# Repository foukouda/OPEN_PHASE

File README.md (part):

<h1 align="center">OPEN_PHASE – PHASETRACKER</h1>

<p align="center">
  3-phase inline current and voltage sensing PCB for BLDC drone motors (INA241A4 + AD7606C-18)
</p>

<p align="center">
  Sub-project of <a href="https://opentruslab.vercel.app/">OPEN THRUST LAB</a>
</p>

<p align="center" width="100%">

</p>

<p align="center">
  
&nbsp; &nbsp; &nbsp; &nbsp;
  
</p>

<p align="center">
  
  <br><sub>Full-resolution video, 60 fps: <a href="Images/OPEN_PHASE.mp4">Images/OPEN_PHASE.mp4</a> (KiCad raytracing, <code>kicad-cli pcb render</code>)</sub>
</p>

***

## OVERVIEW

**OPEN_PHASE** is an open-hardware measurement board developed as part of **OPEN THRUST LAB**, a community-driven project building open-source test benches for drone motor characterization.

The board is inserted between the ESC and a 3-phase BLDC motor (two Amass **MR60PW** connectors) and between the battery and the ESC (two Amass **XT60PW** connectors). On each motor phase (U, V, W) and on the battery line (B) it measures:

- the **current**, with a 1 mΩ four-terminal shunt (Isabellenhütte PBV-R001) and a **TI INA241A4** current-sense amplifier (100 V/V, enhanced PWM rejection, bidirectional around a 2.5 V reference);
- the **voltage**, with a 40.2 kΩ / 10 kΩ divider.

The eight signals are sampled **simultaneously** by an **Analog Devices AD7606C-18** (8 channels, 18 bits, 1 MSPS), so that power, efficiency and ESC behaviour can be computed from time-aligned Vu/Vv/Vw, Iu/Iv/Iw and the battery voltage and current Vb/Ib.

The board only needs **3.3 V**. An LT8362 boost converter (2 MHz) makes 6 V, and two LT3045-1 ultralow-noise LDOs make the analog rails. Each LDO has its SET pin driven by an LTC6655 precision reference, so the LDO works as a low-noise buffer for the reference: **+5VA** (ADC and amplifier supply) and **+2.5VA** (ADC reference and amplifier zero-current level).

> This project was first published as **PhaseSense-8586**, after the first version of the design (INA240 + ADS8586S). The schematic now uses the **INA241A4** and the **AD7606C-18**; everything in this README is taken from the current netlist.

***

## STATUS

This revision has **no ERC / DRC error left**, but it is **not ordered yet**: every fitted part has a manufacturer part number, but there is no firmware. What is in the repository today:

| Area | State |
| --- | --- |
| Analog front-end (shunts, INA241A4, dividers, input filters) | Drawn and routed |
| AD7606C-18 supply, reference and analog inputs | Drawn and routed |
| AD7606C-18 digital interface (CONVST, BUSY, CS, SCLK, SDI, DOUTA–D, RESET, FRSTDATA) | Drawn: software mode (OS0–2 high), serial (PAR/SER SEL high), external reference (REF SELECT low), to the host connector J4. Drawn and routed |
| +3.3V input | J4 pin 1, from the host |
| Power supply (LT8362, LTC6655, LT3045-1) | Drawn and routed. D6 (PMEG2020EH, +3.3V to +5VA) keeps AVCC within 0.3 V of VDRIVE at power-up |
| BOM | Manufacturer and part number on every fitted part (`Manufacturer_Name`, `Manufacturer_Part_Number`). Passives: Murata / Samsung MLCC (C0G for the filters, X7R / X5R rated 16 V or more on the 5–6 V rails), Yageo RC 1 % thick film (the tolerance of simulation 08), Bourns CAT16 arrays. LEDs Würth 150060RS75000, J4 Würth 61301621021 |
| ERC / DRC | ERC 0; DRC 0 errors, 8 warnings (4 copper slivers on In2, 4 footprints edited on the board: IC1, J3, J4, J5); schematic parity 0. CI runs the `PRELIMINARY` variant (no ERC/DRC gate) |

See [DESIGN REVIEW](#design-review) for the points found while documenting and simulating the design.

***

## SPECIFICATIONS

### Electrical specifications

| Parameter | Value |
| --- | --- |
| Input voltage | 3.3 V (LT8362 input range starts at 2.8 V) |
| Boost output — LT8362 | 5.98 V, 2 MHz (RT = 20 kΩ), FBX divider R5/R6 = 1 MΩ / 365 kΩ |
| Analog supply +5VA | 5.000 V — LTC6655-5 (IC7) driving the SET pin of an LT3045-1 (IC8) through R8 = 1 kΩ |
| Reference rail +2.5VA | 2.500 V — LTC6655-2.5 (IC3) driving the SET pin of an LT3045-1 (IC9) through R11 = 1 kΩ |
| Digital supply (AD7606C VDRIVE) | 3.3 V, from the host |
| ADC | AD7606C-18, 8-channel simultaneous sampling, 18 bits, 1 MSPS, external reference on REFIN/REFOUT |
| Current sensing | 4 × PBV-R001 1 mΩ shunt + INA241A4 (100 V/V): **100 mV/A**, zero current = 2.5 V. Version A4 of the silkscreen table, for small motors (1205.5 on 1S); A2 (20 mV/A) for large motors |
| Current range | The amplifier output swing allows about ±23 A (18 A peak in the version table). Connectors: 35 A continuous on the phases (MR60PW), 30 A on the battery line (XT60PW) |
| Voltage sensing | 4 × divider 40.2 kΩ / 10 kΩ: 0.1992 V/V unloaded, **0.1977 V/V** with the AD7606C input impedance |
| Voltage range | 50 V on a ±10 V ADC range (25.2 V for a 6S pack gives 4.98 V) |
| Current channel bandwidth | 17.5 kHz (phase U: R15 = 33 Ω, R16 = 9.1 kΩ, C25 = 1 nF) |
| Voltage channel bandwidth | 48.5 kHz (phase U: divider + Re1 = 1 kΩ, R19 = 9.1 kΩ, C31 = 180 pF) |
| Phase connectors | 2 × Amass MR60PW (J1 = IN-U/V/W from the ESC, J2 = OUT-U/V/W to the motor), 35 A |
| Battery connectors | 2 × Amass XT60PW (J3 = IN-B from the battery, J5 = OUT-B to the ESC), 30 A |

### ADC channel assignment

| AD7606C input | Signal | Source |
| --- | --- | --- |
| V1 | Battery voltage | OUT-B, R32 / R33, Re4, C40, R34 |
| V2 | Battery current | R9 shunt, IC10, R30, C42, R31 |
| V3 | Phase W voltage | OUT-W, R27 / R28, Re3, C34, R29 |
| V4 | Phase W current | R7 shunt, IC6, R25, C33, R26 |
| V5 | Phase V voltage | OUT-V, R22 / R23, Re2, C32, R24 |
| V6 | Phase V current | R4 shunt, IC4, R20, C29, R21 |
| V7 | Phase U voltage | OUT-U, R17 / R18, Re1, C31, R19 |
| V8 | Phase U current | R1 shunt, IC2, R15, C25, R16 |

The four channels are numbered alike: Rn = 33 Ω and Rn+1 = 9.1 kΩ (current filter), Rn+2 / Rn+3 = divider, Rn+4 = 9.1 kΩ (voltage filter), with n = 15 (U), 20 (V), 25 (W), 30 (B). Re1 … Re4 are the 1 kΩ series resistors of the voltage filters.

Current sign: IN+ of each INA241 is on the output side of the shunt (J2 for the phases, J5 for the battery), so a current flowing **from J1 to J2**, or from J3 to J5, **lowers** the output: `V = 2.5 V − 100 mV/A × I(J1→J2)`. The voltage is measured on the same output side of the shunt.

### Power budget

Power chain: **+3.3 V (host) → LT8362 → +6 V → LTC6655 + LT3045-1 → +5VA / +2.5VA**

| Load | Rail | Typical current |
| --- | --- | --- |
| AD7606C-18 AVCC (datasheet: 8.5 mA at 10 kSPS, 45 mA at 1 MSPS) | +5VA | 8.5 – 45 mA |
| 4 × INA241A4 (2.5 mA each) | +5VA | 10 mA |
| 2 × LTC6655 (5 mA each) and 2 × LT3045-1 | +6V | ≈ 13 mA |
| **Total on +6V** (simulated, 1 MSPS) | **+6V** | **68 mA** |
| AD7606C-18 VDRIVE | +3.3V | < 2 mA |
| **Board total** (simulated, 1 MSPS) | **+3.3V** | **≈ 133 mA (0.44 W)** |

### Physical specifications

| Parameter | Value |
| --- | --- |
| Project name | OPEN_PHASE |
| Board name | PHASETRACKER |
| Parent project | OPEN THRUST LAB |
| CAD tool | KiCad 10 |
| Automation tooling | KiBot + GitHub Actions |
| Hardware licence | CERN-OHL-P v2 |
| Dimensions | 65.05 × 77.5 mm |
| Stackup | 4 layers, 1.66 mm, 70 µm outer copper, ENIG |
| Mounting holes | 4 × M3, connected to GND |

***

## SCHEMATIC ARCHITECTURE

Five functional hierarchical sheets (under `Project Architecture`), plus the documentation sheets (Block Diagram, Power - Sequencing, Revision History):

| Sheet (file) | Description |
| --- | --- |
| `AD7606C-18_ADC` (`AD7606C-18 - ADC.kicad_sch`) | AD7606C-18 (IC1). AVCC = +5VA (C20, C35, C38), VDRIVE = +3.3V (C21), REFIN/REFOUT = +2.5VA (C41), REFCAPA/REFCAPB joined on C39 (10 µF), REGCAP pins on C36 / C37 (1 µF each). The eight analog input pairs come from the INA241 sheet through global labels. |
| `INA241_Phase_Sense` (`INA241 - Phase Sensing.kicad_sch`) | Four identical channels: phases U, V, W and the battery line B. Shunt R1 / R4 / R7 / R9 with Kelvin connection to IC2 / IC4 / IC6 / IC10 (INA241A4, VS = +5VA, REF1 = REF2 = +2.5VA), output filter 33 Ω + 1 nF. Voltage divider 40.2 kΩ / 10 kΩ, 1 kΩ + 180 pF. 9.1 kΩ return resistor on every negative ADC input. |
| `Connectors` (`Connectors.kicad_sch`) | J1 and J2, Amass MR60PW: pins 1–3 = phases, mounting pins 4–5 = GND. J3 (XT60PW-F) and J5 (XT60PW-M): pin 2 = battery line, through the shunt R9; pin 1 not connected; mounting pins = GND. J4, 2 × 8 pin header 2.54 mm (horizontal, for Dupont wires) to the host: pin 1 = +3.3V, pins 2, 4, 8, 10 = GND, then CONVST (3), BUSY (5), RESET (6), CS (7), SCLK (9), SDI (11), FRSTDATA (12), DOUTA–D (13–16). |
| `Holes, Fiducials` (`Holes - Fiducials.kicad_sch`) | Four M3 mounting holes H1–H4 connected to GND. |
| `Power_Supply` (`Power Supply - Analog Rails.kicad_sch`) | LT8362 boost (IC5, L1 = 2.2 µH, D2 = PMEG2020EH, 2 MHz, pulse-skipping, soft-start C24 = 10 nF). LTC6655-5 (IC7) and LTC6655-2.5 (IC3) references, each driving the SET pin of an LT3045-1 (IC8 / IC9) through 1 kΩ with 10 µF on SET. PGFB tied to IN (no Power-Good, no fast start-up), ILIM to GND, VIOC open. |

***

## DESIGN REVIEW

Points found while checking the documentation against the netlist and the datasheets, and while simulating the design. Unless marked **Fixed**, none of them has been changed in the schematic: they are design decisions to take.

> Two findings on the +2.5VA rail have been fixed.
>
> **IC3** was an LTC6655**LN**-2.5 wired like the standard part, with pin 6 tied to pin 7. On the LN version pin 6 is NR (noise reduction, to be decoupled to ground), not VOUT_S. IC3 is now a standard **LTC6655-2.5** on the same footprint, for which this wiring is correct. The LTspice model of the LN part does not model the NR pin, so it could not show what the old connection did.
>
> **R12**, on the SET pin of IC9, was 49.9 kΩ. The LT3045-1 sources 100 µA from SET, so the pin wanted 4.99 V against the 2.5 V reference and +2.5VA settled at 2.549 V, outside the 2.495 – 2.505 V reference window of the AD7606C. R12 is now 24.9 kΩ (100 µA × 24.9 kΩ = 2.49 V): +2.5VA settles at 2.4996 V.

| # | Finding | Evidence | Suggested action |
| --- | --- | --- | --- |
| 1 | **The AD7606C-18 has no digital interface and the board has no +3.3V input.** CONVST, BUSY, CS, RD/SCLK, DOUTA–D, FRSTDATA, RESET, OS0–2, RANGE, PAR/SER SEL, STBY, WR and REF SELECT are open. | Netlist: 32 `unconnected-(IC1-…)` nets; J1 / J2 and J3 / J5 only carry the phases, the battery line and GND. | **Fixed**: host connector J4 added, mode pins strapped (software mode, serial, REF SELECT low). |
| 2 | **AD7606C-18 pins left open that the datasheet asks to connect**: AGND pin 26 and REFGND pin 46 (*"All six of the AGND pins must connect to the AGND plane"*). | Netlist: `unconnected-(IC1-AGND_2-Pad26)`, `…REFGND_2-Pad46`. | **Fixed**: both on GND. |
| 3 | **INA241A2 pin 4 (NC) is open** on IC2, IC4, IC6 and IC10. The datasheet pin table says: *"NC — Reserved. Connect to ground."* | Netlist: `unconnected-(IC2-NC-Pad4)` and the same for IC4, IC6, IC10. | **Fixed**: pin 4 tied to GND on the four INA241 (schematic and PCB). |
| 4 | **The INA241A2 gain is 20 V/V.** The schematic note listed the INA240 gains (A2 = 50 V/V). With 1 mΩ the scale is 20 mV/A: 35 A only uses ±0.7 V of the ±2.5 V available. | TI datasheet SBOSA30D: A1 = 10, A2 = 20, A3 = 50, A4 = 100, A5 = 200 V/V. The note is corrected in the schematic. | **Changed**: INA241A4 (100 V/V, ±23 A) fitted for small motors; the silkscreen table lists the other versions. |
| 5 | **Current channels: the 9.1 kΩ return resistor creates a 15 mV offset.** The AD7606C inputs are 1.2 MΩ to an internal 2 V node. On the voltage channels both inputs see about 9 kΩ, so the two bias drops cancel (−0.15 mV). On the current channels the positive input sees 33 Ω and the negative one 9.1 kΩ: V− sits at +15 mV. | Simulation 06: 2.4849 V at zero current instead of 2.5000 V, which reads as +0.15 A with the INA241A4 (+0.75 A with the A2). | Constant offset: remove it with a zero-current calibration. Do not shrink R16 / R21 / R26 / R31 without recomputing the filter: the capacitor is differential, so they set the 17.5 kHz corner. |
| 6 | **Voltage channels: −0.75 % gain error** from the 9 kΩ source impedance into the 1.2 MΩ input (−0.9 % at the 1 MΩ minimum). | Simulation 05: 0.1977 V/V instead of 0.1992 V/V. | Calibrate, or use the AD7606C per-channel gain register (software mode, 9 kΩ). |
| 7 | **PCB not finished**: IC5, L1 and the boost passives are outside the board outline, C16 has no schematic symbol, C14 / C15 / C39 use a 4-pin capacitor symbol on a 2-pad footprint. | DRC: 37 unconnected items, 20 schematic parity warnings. | **Fixed**: boost stage placed and routed; C14 / C15 / C39 on a 4-pad 0805 footprint (pads 3 / 4 stacked on 2 / 1). |
| 8 | **The delay between the current and voltage readings is not known before a board exists.** The current channel has a 17.5 kHz filter and the voltage channel a 48.5 kHz one, and the inductance of the shunt (datasheet: below 10 nH) acts against the filter of the current channel. Under PWM, a phase difference between the two readings at the switching frequency turns reactive power into measured power. | Simulation 07 (1205.5-class motor on 1S, 3.5 kHz electrical), phase power after DC calibration: −19.0 % with 0 nH, −5.0 % with 5 nH, +9.0 % with 10 nH. With a time shift of the current calibrated at the electrical frequency: −3.5 … −2.5 %. | Measure the phase between the two channels on the first board, then choose C31 / C32 / C34 or correct the delay in the firmware. |
| 9 | **AD7606C-18 VDRIVE is above AVCC + 0.3 V at power-up.** VDRIVE = +3.3V comes from the host and is there at once, while AVCC = +5VA (boost, then LTC6655 + LT3045-1) only passes 3.0 V after about 10 ms. | Datasheet Rev. B, Table 6: *"VDRIVE to AGND −0.3 V to AVCC + 0.3 V"*. | **Fixed**: D6, PMEG2020EH low-Vf Schottky from +3.3V (anode) to +5VA (cathode), under IC1 on the bottom side; reverse-biased in operation. |

***

## SIMULATION (LTspice)

The power chain and the two measurement channels are simulated with **LTspice 26** in [`Simulation/LTspice/`](Simulation/LTspice). Every component value comes from the KiCad netlist and keeps its reference designator, so the simulation schematics can be read side by side with the KiCad sheets.

| File | Analysis | What it checks |
| --- | --- | --- |
| `01_Power_Chain_Startup.asc` | `.tran` 12 ms, switching | +3.3V → LT8362 → +6V → LT3045-1 soft-start, inrush and inductor current (board as built) |
| `02_Analog_Rails_Startup.asc` | `.tran` 150 ms | Settling and accuracy of +5VA and +2.5VA |
| `03_Boost_Ripple.asc` | `.tran` 6 ms, switching | LT8362 steady-state ripple on +6V with the simulated load of both rails |
| `04_Analog_Rails_PSRR.asc` | `.ac` 10 Hz – 10 MHz | Rejection from +6V to +5VA and +2.5VA (reference + LDO, board capacitors) |
| `05_Measurement_Channels_AC.asc` | `.ac` 10 Hz – 10 MHz | Gain and bandwidth of the current and voltage channels, down to the ADC pins |
| `06_Measurement_Channels_Step.asc` | `.tran` 600 µs | DC transfer, offsets and settling for a 25.2 V and an 18 A step |
| `07_Measurement_Quality_Waveforms.asc` | `.tran` 8 ms, 3 runs | ESC PWM voltage and motor current through both channels of phase U, battery voltage and current through the battery channels: readings against the truth, for a shunt inductance of 0, 5 and 10 nH |
| `08_Measurement_Quality_Tolerances.asc` | `.dc`, 1000 runs | Monte Carlo on the tolerances: spread of offset and gain before calibration |

**Models**

- **LT8362, LT3045-1, LTC6655-5, LTC6655-2.5**: official Analog Devices models shipped with LTspice.
- **INA241A4**: TI does not provide an LTspice model, so `INA241A4_behav.sub` / `.asy` is a **behavioral model** written for this project from the datasheet (SBOSA30D): gain 100 V/V around (REF1 + REF2) / 2, 1.1 MHz bandwidth, 8 V/µs slew rate, output swing, 2.5 mA supply current, 35 µA input bias. Gain and input offset are parameters, nominal except in simulation 08. It does not model noise, CMRR or the 1 µs output hold of the enhanced PWM rejection.
- **AD7606C-18**: loads only. AVCC and VDRIVE are current sources (45 mA and 1.8 mA, the 1 MSPS figures). Each analog input is 1.2 MΩ to an internal 2 V node plus 5 pF, from the datasheet (*"Analog Input Current = (VIN − 2)/RIN"*).
- **D2**: PMEG2020EH modelled with the LTspice PMEG2020AEA (same 20 V / 2 A Nexperia MEGA Schottky family). **L1**: 2.2 µH, 22 mΩ (Würth WE-MAPI 4030, 74438357022).
- Ceramic capacitors use their nominal value (no DC-bias derating).

**Results**

| Quantity | Simulated | Notes |
| --- | --- | --- |
| +6V output (LT8362) | 5.96 V | 1.6 V × (1 + 1 MΩ / 365 kΩ) = 5.98 V |
| +6V reaches 90 % | 0.88 ms | 5.9 V after 1.0 ms, 6.04 V overshoot |
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
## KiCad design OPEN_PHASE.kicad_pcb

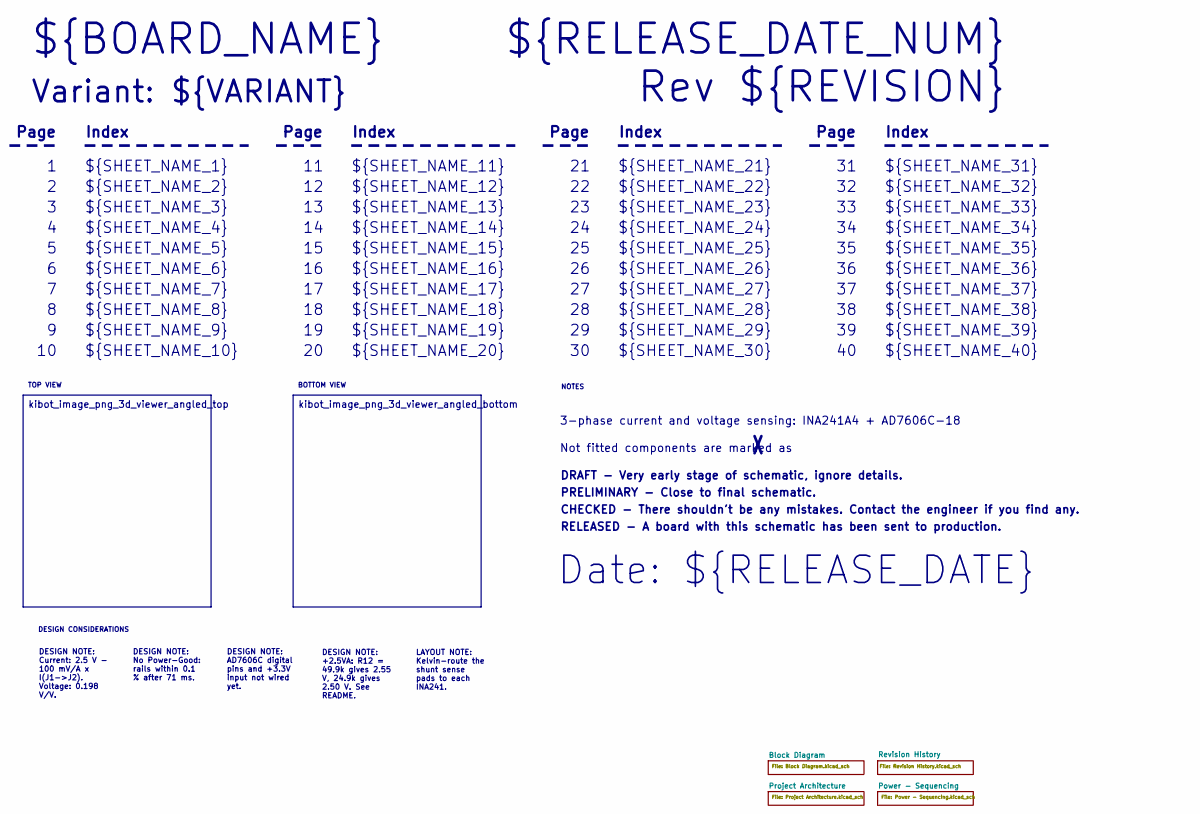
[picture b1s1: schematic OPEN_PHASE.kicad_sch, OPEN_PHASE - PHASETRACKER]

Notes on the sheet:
Variant: ${VARIANT}
RELEASED - A board with this schematic has been sent to production.
${SHEET_NAME_24}
Index
Page
PRELIMINARY - Close to final schematic.
${SHEET_NAME_22}
DRAFT - Very early stage of schematic, ignore details.
${SHEET_NAME_12}
${SHEET_NAME_8}
${SHEET_NAME_2}
${SHEET_NAME_5}
${SHEET_NAME_20}
${SHEET_NAME_23}
${RELEASE_DATE_NUM}
${SHEET_NAME_35}
Not fitted components are marked as
${SHEET_NAME_11}
${SHEET_NAME_6}
${SHEET_NAME_37}
${SHEET_NAME_26}
${SHEET_NAME_36}
Rev ${REVISION}
${SHEET_NAME_15}
CHECKED - There shouldn't be any mistakes. Contact the engineer if you find any.
${SHEET_NAME_14}
${SHEET_NAME_21}
${SHEET_NAME_17}
${SHEET_NAME_18}
Date: ${RELEASE_DATE}
${SHEET_NAME_7}
${SHEET_NAME_31}
${BOARD_NAME}
${SHEET_NAME_40}
${SHEET_NAME_39}
${SHEET_NAME_32}
${SHEET_NAME_1}
${SHEET_NAME_9}
${SHEET_NAME_38}
${SHEET_NAME_29}

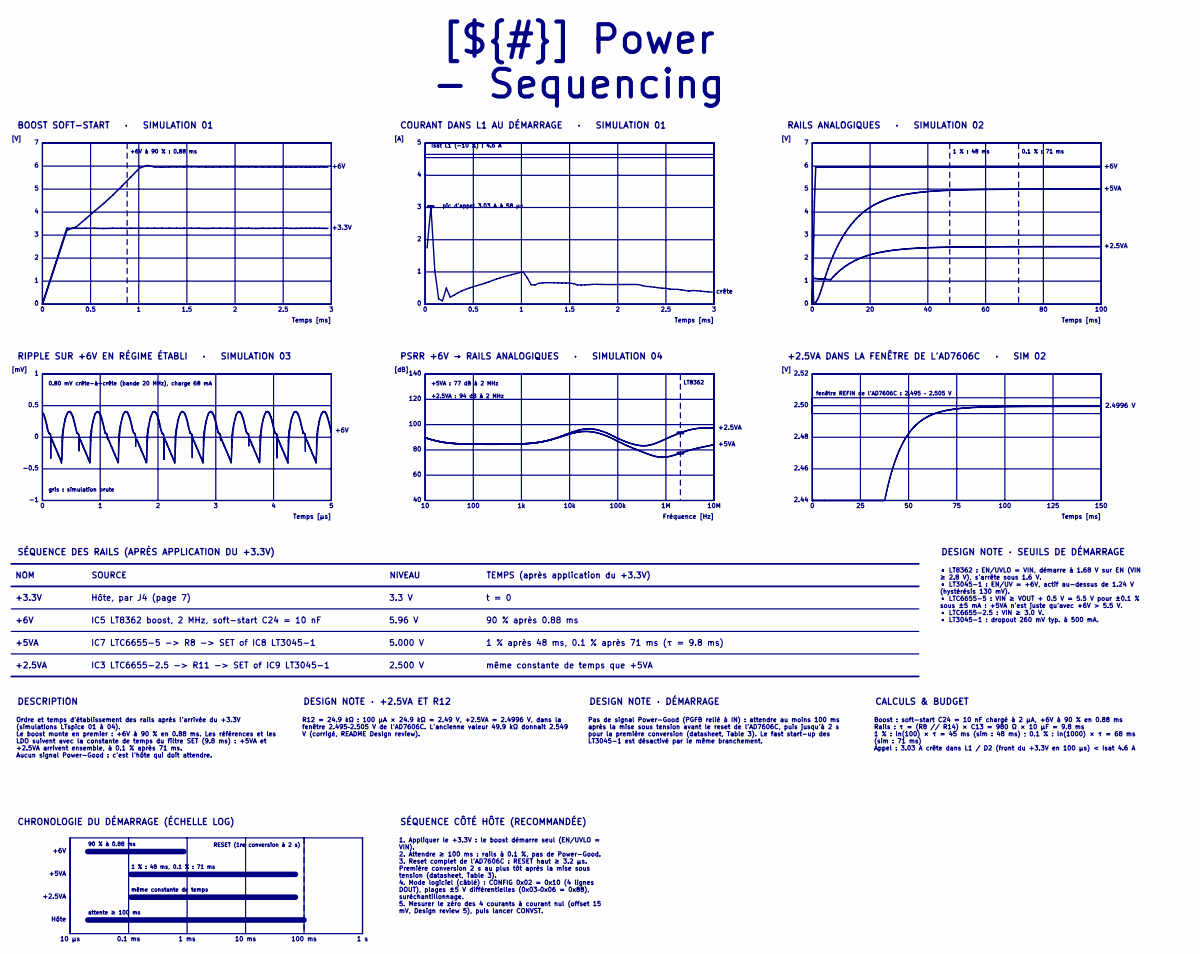
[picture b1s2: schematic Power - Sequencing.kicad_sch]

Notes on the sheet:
[A]
+6V
2.4996 V
gris : simulation brute
5.96 V
0.1 % : 71 ms
+2.5VA
attente ≥ 100 ms
même constante de temps
0.80 mV crête-à-crête (bande 20 MHz), charge 68 mA
0.5
150
100
2.5
2.46
t = 0
90 % à 0.88 ms
Isat L1 (−10 %) : 4.6 A
NIVEAU
+5VA
TEMPS (après application du +3.3V)
fenêtre REFIN de l'AD7606C : 2.495 – 2.505 V
10 µs
[V]
Temps [ms]
0.1 ms
100k
1 ms
Hôte
IC3 LTC6655-2.5 -> R11 -> SET of IC9 LT3045-1
1.5
125
crête
90 % après 0.88 ms
100 ms
+5VA : 77 dB à 2 MHz
SOURCE
3.3 V
2.44
2.500 V

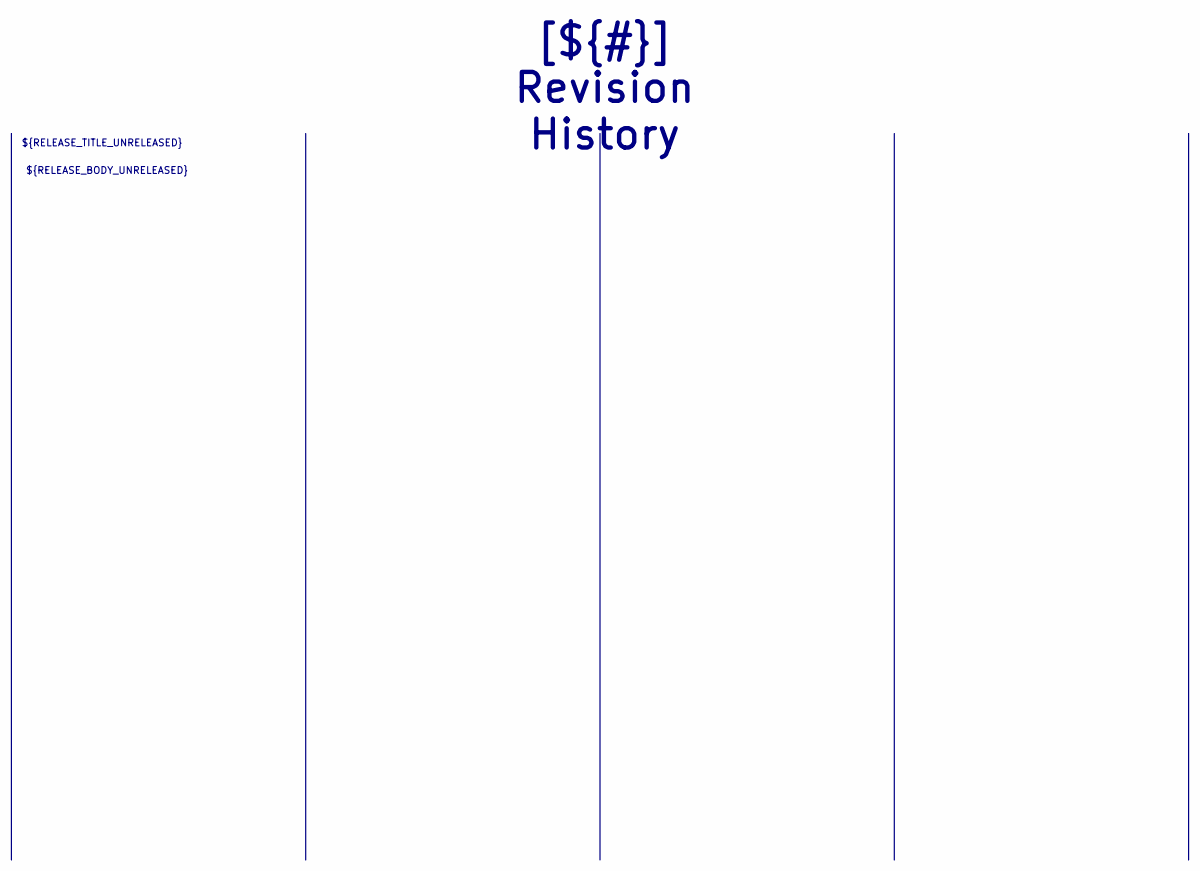
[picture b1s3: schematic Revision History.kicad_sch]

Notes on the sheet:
[${#}] ${TITLE}
${RELEASE_BODY_UNRELEASED}
${RELEASE_TITLE_UNRELEASED}

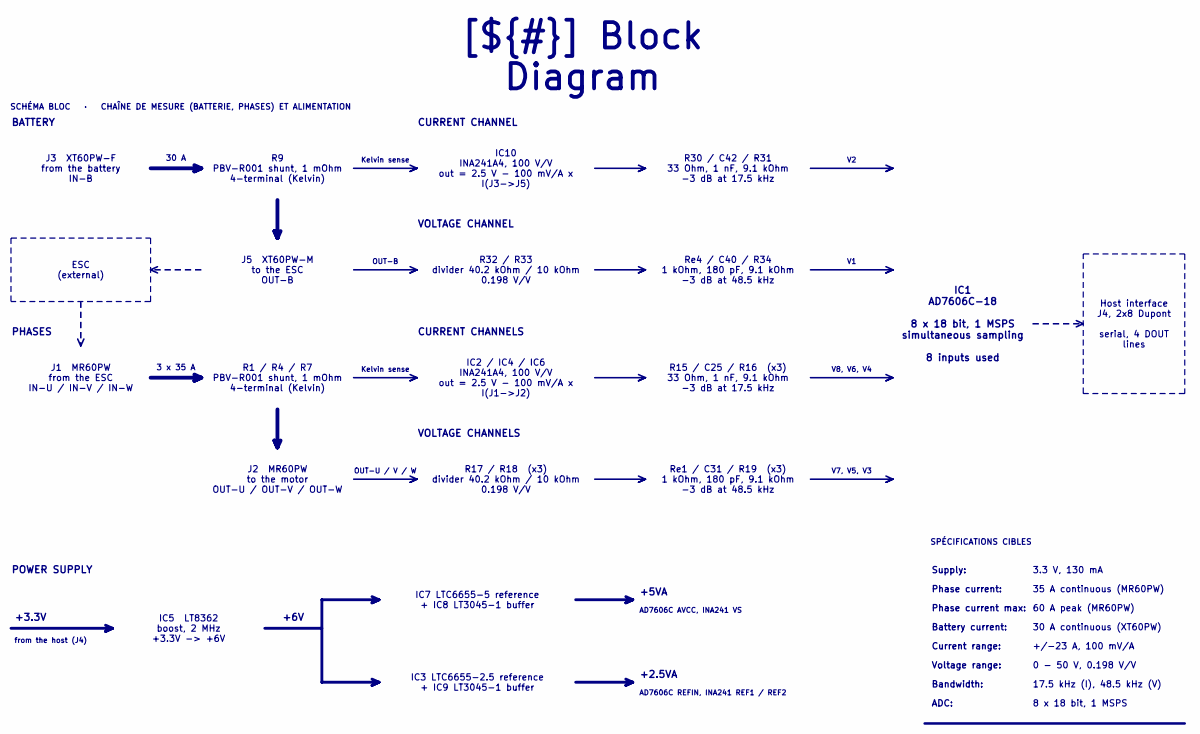
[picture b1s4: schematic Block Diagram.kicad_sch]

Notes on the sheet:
Supply:
+2.5VA
+5VA
Kelvin sense
VOLTAGE CHANNEL
CURRENT CHANNELS
CURRENT CHANNEL
Phase current max:
30 A continuous (XT60PW)
Voltage range:
8 x 18 bit, 1 MSPS
Current range:
35 A continuous (MR60PW)
3.3 V, 130 mA
17.5 kHz (I), 48.5 kHz (V)
Battery current:
+3.3V
ADC:
Bandwidth:
Phase current:
+6V
VOLTAGE CHANNELS
PHASES
V7, V5, V3
3 x 35 A
V8, V6, V4
BATTERY
AD7606C REFIN, INA241 REF1 / REF2
+/-23 A, 100 mV/A
OUT-U / V / W
30 A
POWER SUPPLY
0 - 50 V, 0.198 V/V
AD7606C AVCC, INA241 VS
OUT-B
from the host (J4)
60 A peak (MR60PW)
R32 / R33 divider 40.2 kOhm / 10 kOhm 0.198 V/V
R9 PBV-R001 shunt, 1 mOhm 4-terminal (Kelvin)
Re1 / C31 / R19 (x3) 1 kOhm, 180 pF, 9.1 kOhm -3 dB at 48.5 kHz

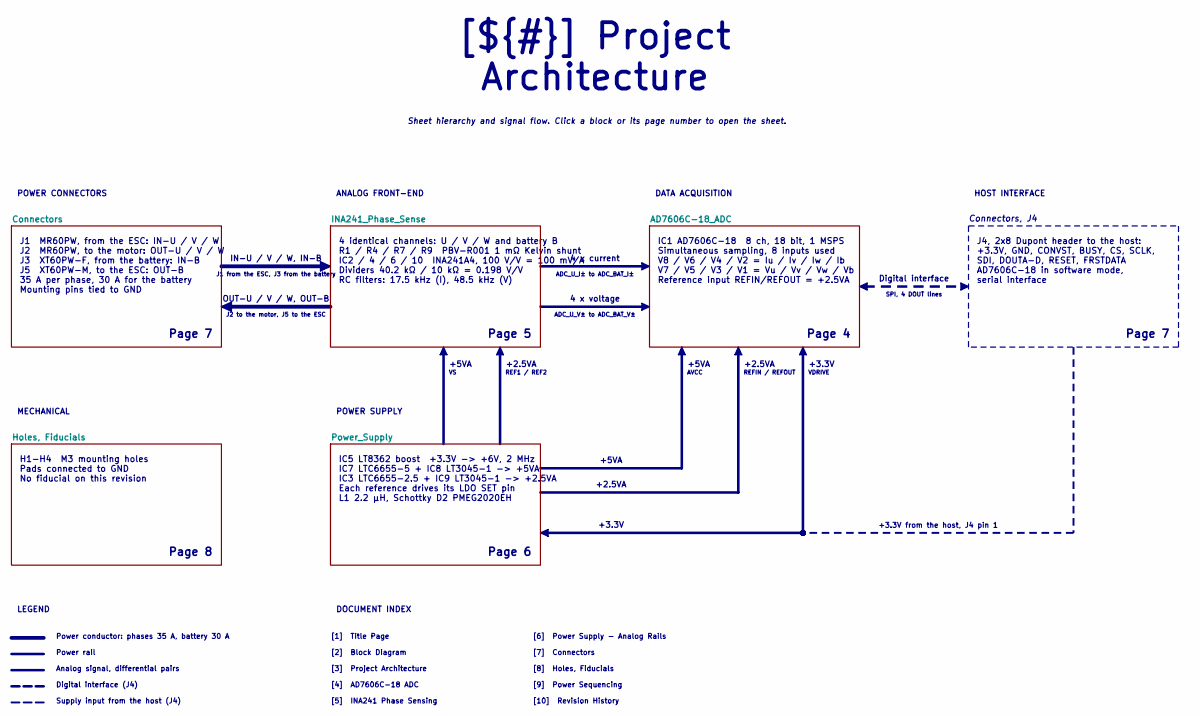
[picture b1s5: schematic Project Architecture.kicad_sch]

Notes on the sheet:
+3.3V
IC5 LT8362 boost +3.3V -> +6V, 2 MHz IC7 LTC6655-5 + IC8 LT3045-1 -> +5VA IC3 LTC6655-2.5 + IC9 LT3045-1 -> +2.5VA Each reference drives its LDO SET pin L1 2.2 µH, Schottky D2 PMEG2020EH
SPI, 4 DOUT lines
4 x current
ADC_U_V± to ADC_BAT_V±
AVCC
ADC_U_I± to ADC_BAT_I±
+5VA
Digital interface
[10] Revision History
[3] Project Architecture
Sheet hierarchy and signal flow. Click a block or its page number to open the sheet.
+3.3V from the host, J4 pin 1
Page 8
+2.5VA
Analog signal, differential pairs
[2] Block Diagram
[4] AD7606C-18 ADC
Supply input from the host (J4)
Page 4
Page 7
[1] Title Page
J1 from the ESC, J3 from the battery
[8] Holes, Fiducials
H1-H4 M3 mounting holes Pads connected to GND No fiducial on this revision
Digital interface (J4)
Connectors, J4
Power rail
Power conductor: phases 35 A, battery 30 A
Page 5
[9] Power Sequencing
IC1 AD7606C-18 8 ch, 18 bit, 1 MSPS Simultaneous sampling, 8 inputs used V8 / V6 / V4 / V2 = Iu / Iv / Iw / Ib V7 / V5 / V3 / V1 = Vu / Vv / Vw / Vb Reference input REFIN/REFOUT = +2.5VA
J2 to the motor, J5 to the ESC
4 x voltage
[7] Connectors
REFIN / REFOUT
Page 6
IN-U / V / W, IN-B
VDRIVE
[6] Power Supply - Analog Rails

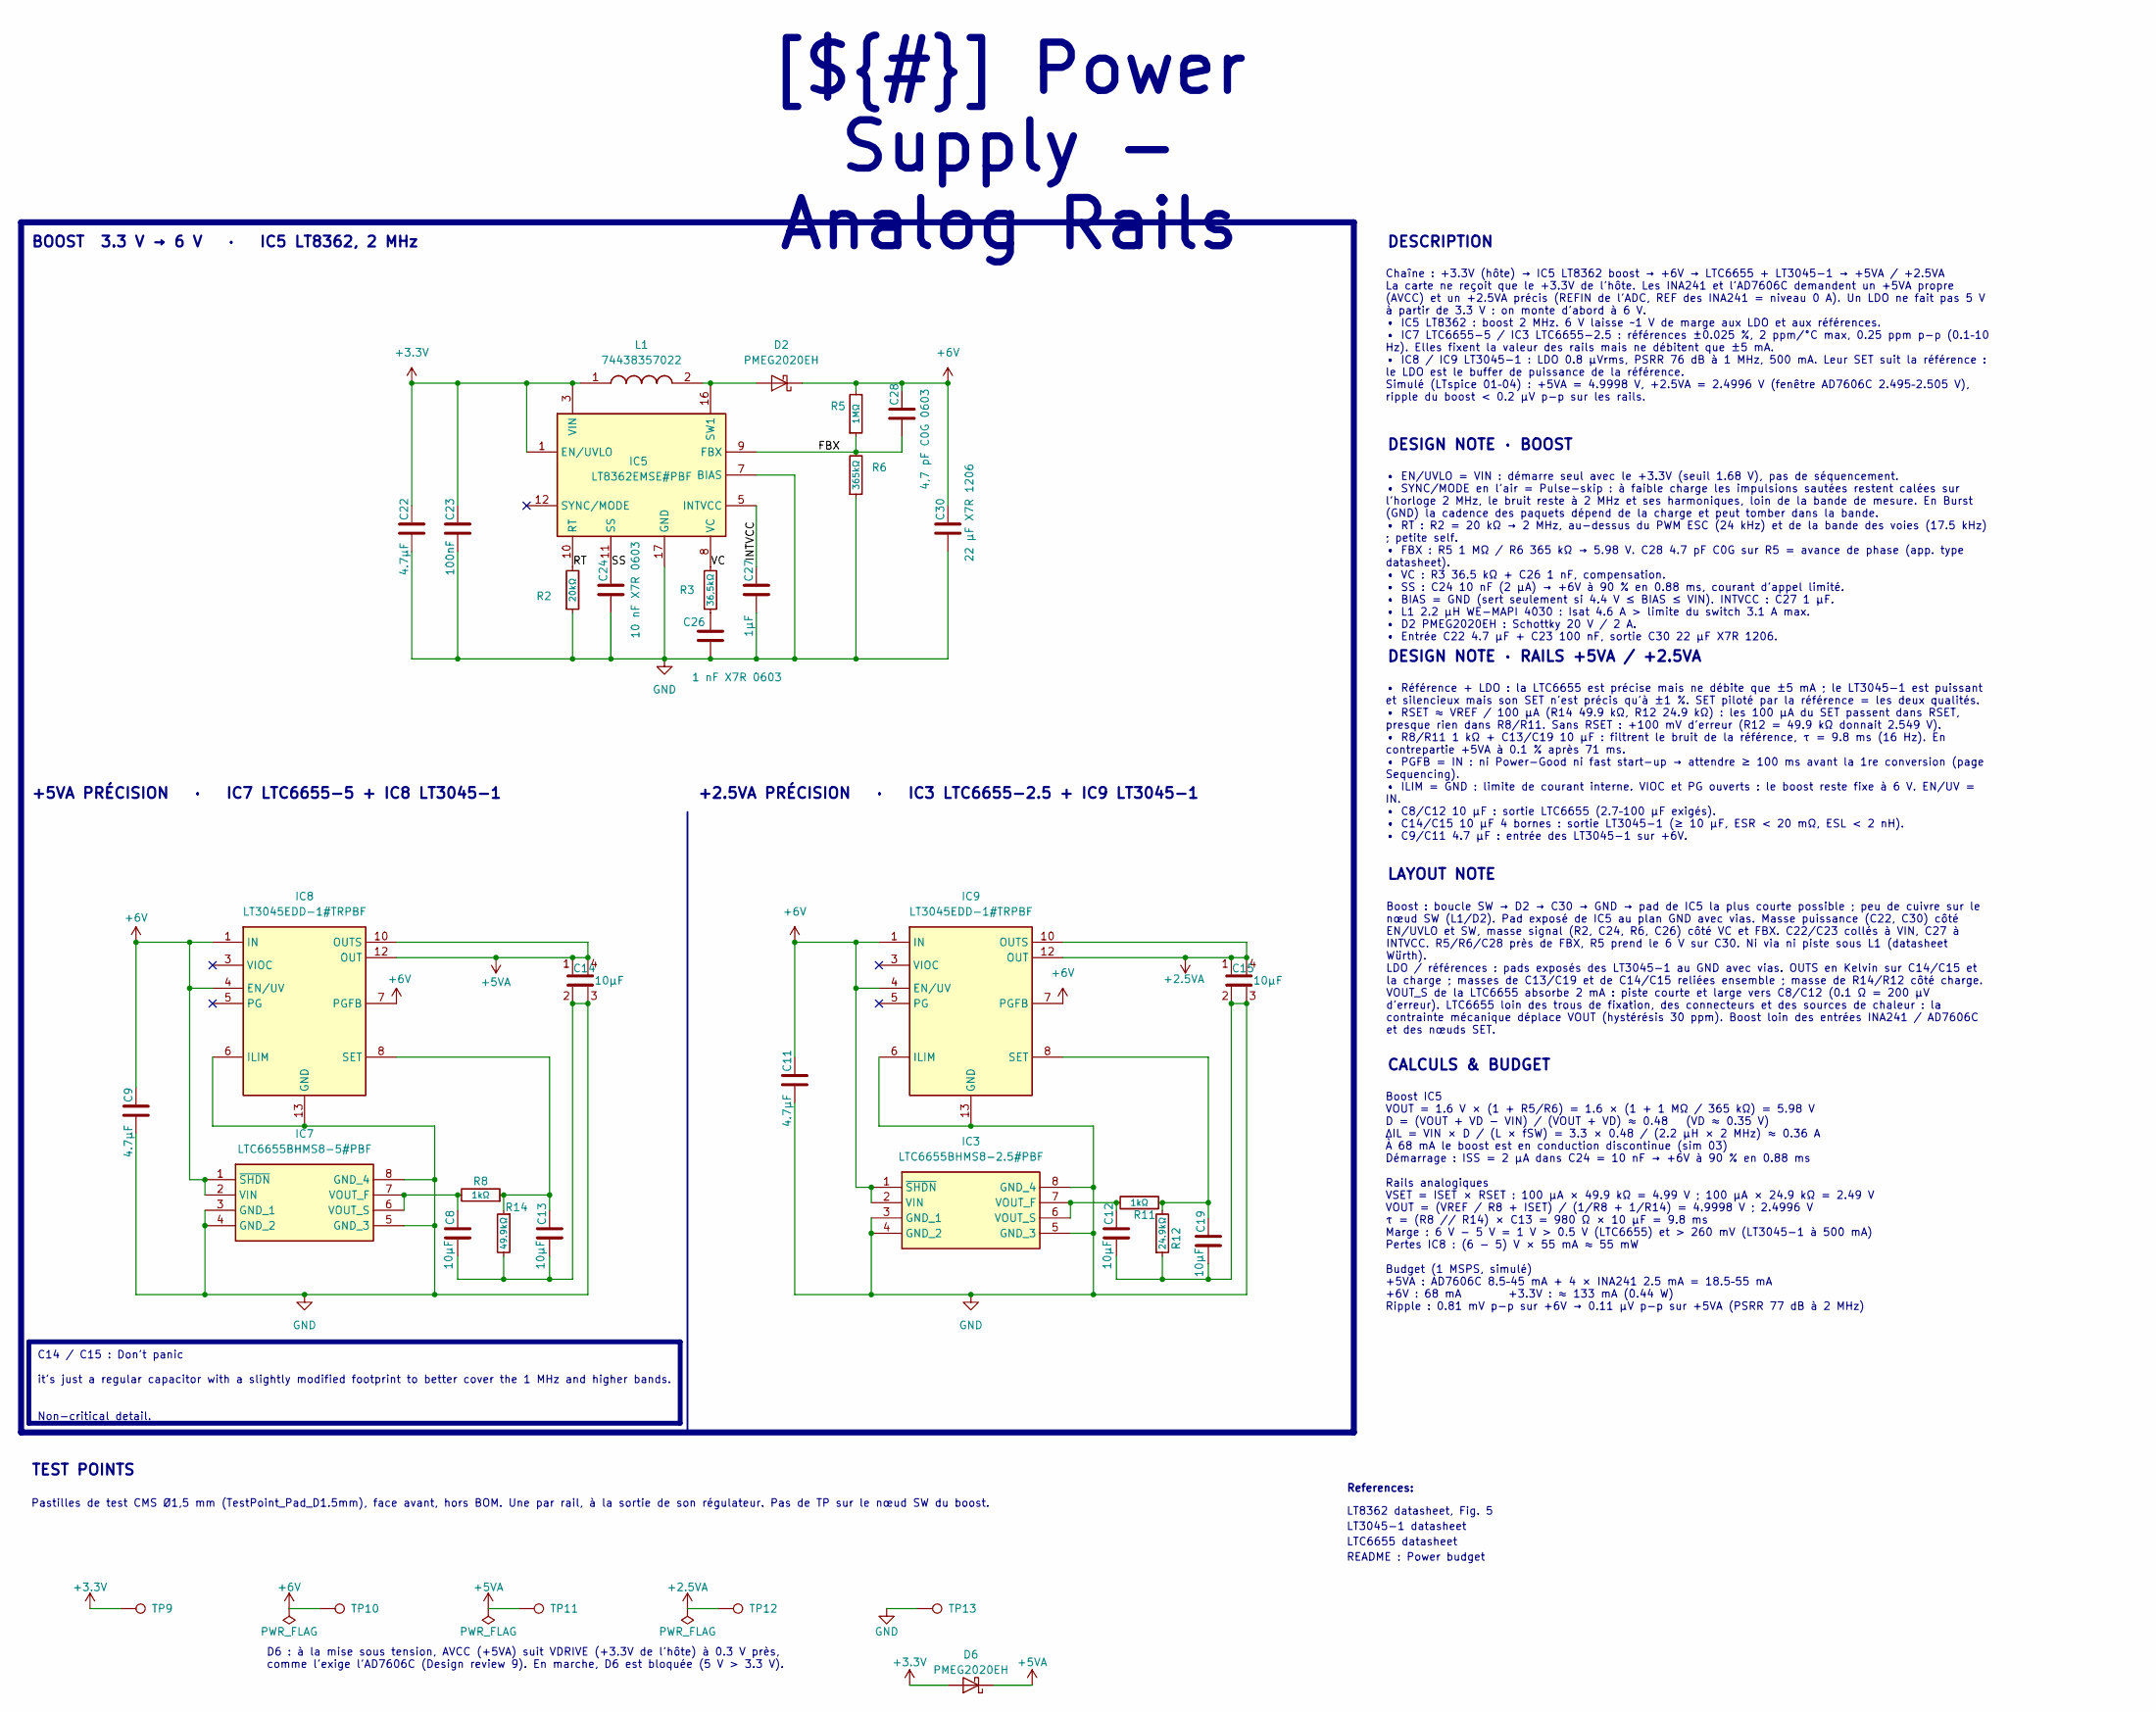
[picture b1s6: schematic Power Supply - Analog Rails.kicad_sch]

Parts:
C8, C12: 10µF; C_0603_1608Metric; Manufacturer_Part_Number CL10A106KO8NQNC
C9, C11, C22: 4.7µF; C_0603_1608Metric; Manufacturer_Part_Number GRM188R61E475KE11D
C13, C19: 10µF; C_0805_2012Metric; Manufacturer_Part_Number CL21B106KOQNNNE
C14, C15: 10µF; C_0805_2012Metric_4T; Manufacturer_Part_Number CL21B106KOQNNNE
C23: 100nF; C_0603_1608Metric; Manufacturer_Part_Number GRM188R71H104KA93D
C24: 10 nF X7R 0603; C_0603_1608Metric; Manufacturer_Part_Number GRM188R71H103KA01D
C26: 1 nF X7R 0603; C_0603_1608Metric; Manufacturer_Part_Number GRM188R71H102KA01D
C27: 1µF; C_0603_1608Metric; Manufacturer_Part_Number GRM188R71E105KA12D
C28: 4,7 pF C0G 0603; C_0603_1608Metric; Manufacturer_Part_Number CC0603CRNPO9BN4R7
C30: 22 µF X7R 1206; C_1206_3216Metric_Pad1.33x1.80mm_HandSolder; Manufacturer_Part_Number GRM31CZ71C226ME15L
D2, D6: PMEG2020EH; D_SOD-123F; Manufacturer_Part_Number PMEG2020EH,115
IC3: LTC6655BHMS8-2.5#PBF; SOP65P490X110-8N; Manufacturer_Part_Number LTC6655BHMS8-2.5#PBF
IC5: LT8362EMSE#PBF; LT8362EMSEPBF; Manufacturer_Part_Number LT8362EMSE#PBF; Mouser Part Number 584-LT8362EMSEPBF
IC7: LTC6655BHMS8-5#PBF; SOP65P490X110-8N; Manufacturer_Part_Number LTC6655BHMS8-5#PBF; Mouser Part Number 584-C6655BHMS8-5PBF
IC8, IC9: LT3045EDD-1#TRPBF; SON45P300X300X80-13N-D; Manufacturer_Part_Number LT3045EDD-1#TRPBF; Mouser Part Number 584-LT3045EDD-1TRPBF
L1: 74438357022; L_Wuerth_MAPI-4030; Manufacturer_Part_Number 74438357022; Mouser Part Number 710-74438357022
R2: 20kΩ; R_0603_1608Metric; Manufacturer_Part_Number RC0603FR-0720KL
R3: 36,5kΩ; R_0603_1608Metric; Manufacturer_Part_Number RC0603FR-0736K5L
R5: 1MΩ; R_0603_1608Metric; Manufacturer_Part_Number RC0603FR-071ML
R6: 365kΩ; R_0603_1608Metric; Manufacturer_Part_Number RC0603FR-07365KL
R8, R11: 1kΩ; R_0603_1608Metric; Manufacturer_Part_Number RC0603FR-071KL
R12: 24.9kΩ; R_0603_1608Metric; Manufacturer_Part_Number RC0603FR-0724K9L
R14: 49.9kΩ; R_0603_1608Metric; Manufacturer_Part_Number RC0603FR-0749K9L
TP9, TP10, TP11, TP12, TP13: TestPoint; TestPoint_Pad_D1.5mm

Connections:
+2.5VA: C15.1, C15.4, IC9.10 (OUTS), IC9.11 (OUT_2), IC9.12 (OUT), TP12.1 (1_1); also elsewhere on the board
+3.3V: C22.1, C23.1, D6.2 (A), IC5.1 (EN/UVLO), IC5.3 (VIN), L1.1, TP9.1 (1_1); also elsewhere on the board
+5VA: C14.1, C14.4, D6.1 (K), IC8.10 (OUTS), IC8.11 (OUT_2), IC8.12 (OUT), TP11.1 (1_1); also elsewhere on the board
+6V: C9.1, C11.1, C28.1, C30.1, D2.1 (K), IC3.1 (~SHDN), IC3.2 (VIN), IC7.1 (~SHDN), IC7.2 (VIN), IC8.1 (IN), IC8.2 (IN_2), IC8.4 (EN/UV), IC8.7 (PGFB), IC9.1 (IN), IC9.2 (IN_2), IC9.4 (EN/UV), IC9.7 (PGFB), R5.1, TP10.1 (1_1); also elsewhere on the board
/Project Architecture/Power_Supply/FBX: C28.2, IC5.9 (FBX), R5.2, R6.1
/Project Architecture/Power_Supply/INTVCC: C27.1, IC5.5 (INTVCC)
/Project Architecture/Power_Supply/RT: IC5.10 (RT), R2.1
/Project Architecture/Power_Supply/SS: C24.1, IC5.11 (SS)
/Project Architecture/Power_Supply/VC: IC5.8 (VC), R3.1
GND: C8.2, C9.2, C11.2, C12.2, C13.2, C14.2, C14.3, C15.2, C15.3, C19.2, C22.2, C23.2, C24.2, C26.1, C27.2, C30.2, IC3.3 (GND_1), IC3.4 (GND_2), IC3.5 (GND_3), IC3.8 (GND_4), IC5.7 (BIAS), IC5.17 (GND), IC7.3 (GND_1), IC7.4 (GND_2), IC7.5 (GND_3), IC7.8 (GND_4), IC8.6 (ILIM), IC8.9 (GND_1), IC8.13 (GND), IC9.6 (ILIM), IC9.9 (GND_1), IC9.13 (GND), R2.2, R6.2, R12.2, R14.1, TP13.1 (1_1); also elsewhere on the board
unnamed: C26.2, R3.2
unnamed: D2.2 (A), IC5.14 (SW2), IC5.16 (SW1), L1.2
unnamed: C12.1, IC3.6 (VOUT_S), IC3.7 (VOUT_F), R11.1
unnamed: C8.1, IC7.6 (VOUT_S), IC7.7 (VOUT_F), R8.1
unnamed: C13.1, IC8.8 (SET), R8.2, R14.2
unnamed: C19.1, IC9.8 (SET), R11.2, R12.1

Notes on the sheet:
README : Power budget
LT3045-1 datasheet
References:
LT8362 datasheet, Fig. 5
LTC6655 datasheet
• Référence + LDO : la LTC6655 est précise mais ne débite que ±5 mA ; le LT3045-1 est puissant et silencieux mais son SET n'est précis qu'à ±1 %. SET piloté par la référence = les deux qualités. • RSET ≈ VREF / 100 µA (R14 49.9 kΩ, R12 24.9 kΩ) : les 100 µA du SET passent dans RSET, presque rien da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
Boost IC5 VOUT = 1.6 V × (1 + R5/R6) = 1.6 × (1 + 1 MΩ / 365 kΩ) = 5.98 V D = (VOUT + VD − VIN) / (VOUT + VD) ≈ 0.48 (VD ≈ 0.35 V) ΔIL = VIN × D / (L × fSW) = 3.3 × 0.48 / (2.2 µH × 2 MHz) ≈ 0.36 A À 68 mA le boost est en conduction discontinue (sim 03) Démarrage : ISS = 2 µA dans C24 = 10 nF → +6V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
[${#}] ${TITLE}
Boost : boucle SW → D2 → C30 → GND → pad de IC5 la plus courte possible ; peu de cuivre sur le nœud SW (L1/D2). Pad exposé de IC5 au plan GND avec vias. Masse puissance (C22, C30) côté EN/UVLO et SW, masse signal (R2, C24, R6, C26) côté VC et FBX. C22/C23 collés à VIN, C27 à INTVCC. R5/R6/C28 près 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
C14 / C15 : Don't panic it's just a regular capacitor with a slightly modified footprint to better cover the 1 MHz and higher bands. Non-critical detail.
DESIGN NOTE · BOOST
BOOST 3.3 V → 6 V · IC5 LT8362, 2 MHz
+2.5VA PRÉCISION · IC3 LTC6655-2.5 + IC9 LT3045-1
LAYOUT NOTE
TEST POINTS
CALCULS & BUDGET
DESCRIPTION
Pastilles de test CMS Ø1,5 mm (TestPoint_Pad_D1.5mm), face avant, hors BOM. Une par rail, à la sortie de son régulateur. Pas de TP sur le nœud SW du boost.
• EN/UVLO = VIN : démarre seul avec le +3.3V (seuil 1.68 V), pas de séquencement. • SYNC/MODE en l'air = Pulse-skip : à faible charge les impulsions sautées restent calées sur l'horloge 2 MHz, le bruit reste à 2 MHz et ses harmoniques, loin de la bande de mesure. En Burst (GND) la cadence des paque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
Chaîne : +3.3V (hôte) → IC5 LT8362 boost → +6V → LTC6655 + LT3045-1 → +5VA / +2.5VA La carte ne reçoit que le +3.3V de l'hôte. Les INA241 et l'AD7606C demandent un +5VA propre (AVCC) et un +2.5VA précis (REFIN de l'ADC, REF des INA241 = niveau 0 A). Un LDO ne fait pas 5 V à partir de 3.3 V : on mon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
+5VA PRÉCISION · IC7 LTC6655-5 + IC8 LT3045-1
DESIGN NOTE · RAILS +5VA / +2.5VA
D6 : à la mise sous tension, AVCC (+5VA) suit VDRIVE (+3.3V de l'hôte) à 0.3 V près, comme l'exige l'AD7606C (Design review 9). En marche, D6 est bloquée (5 V > 3.3 V).

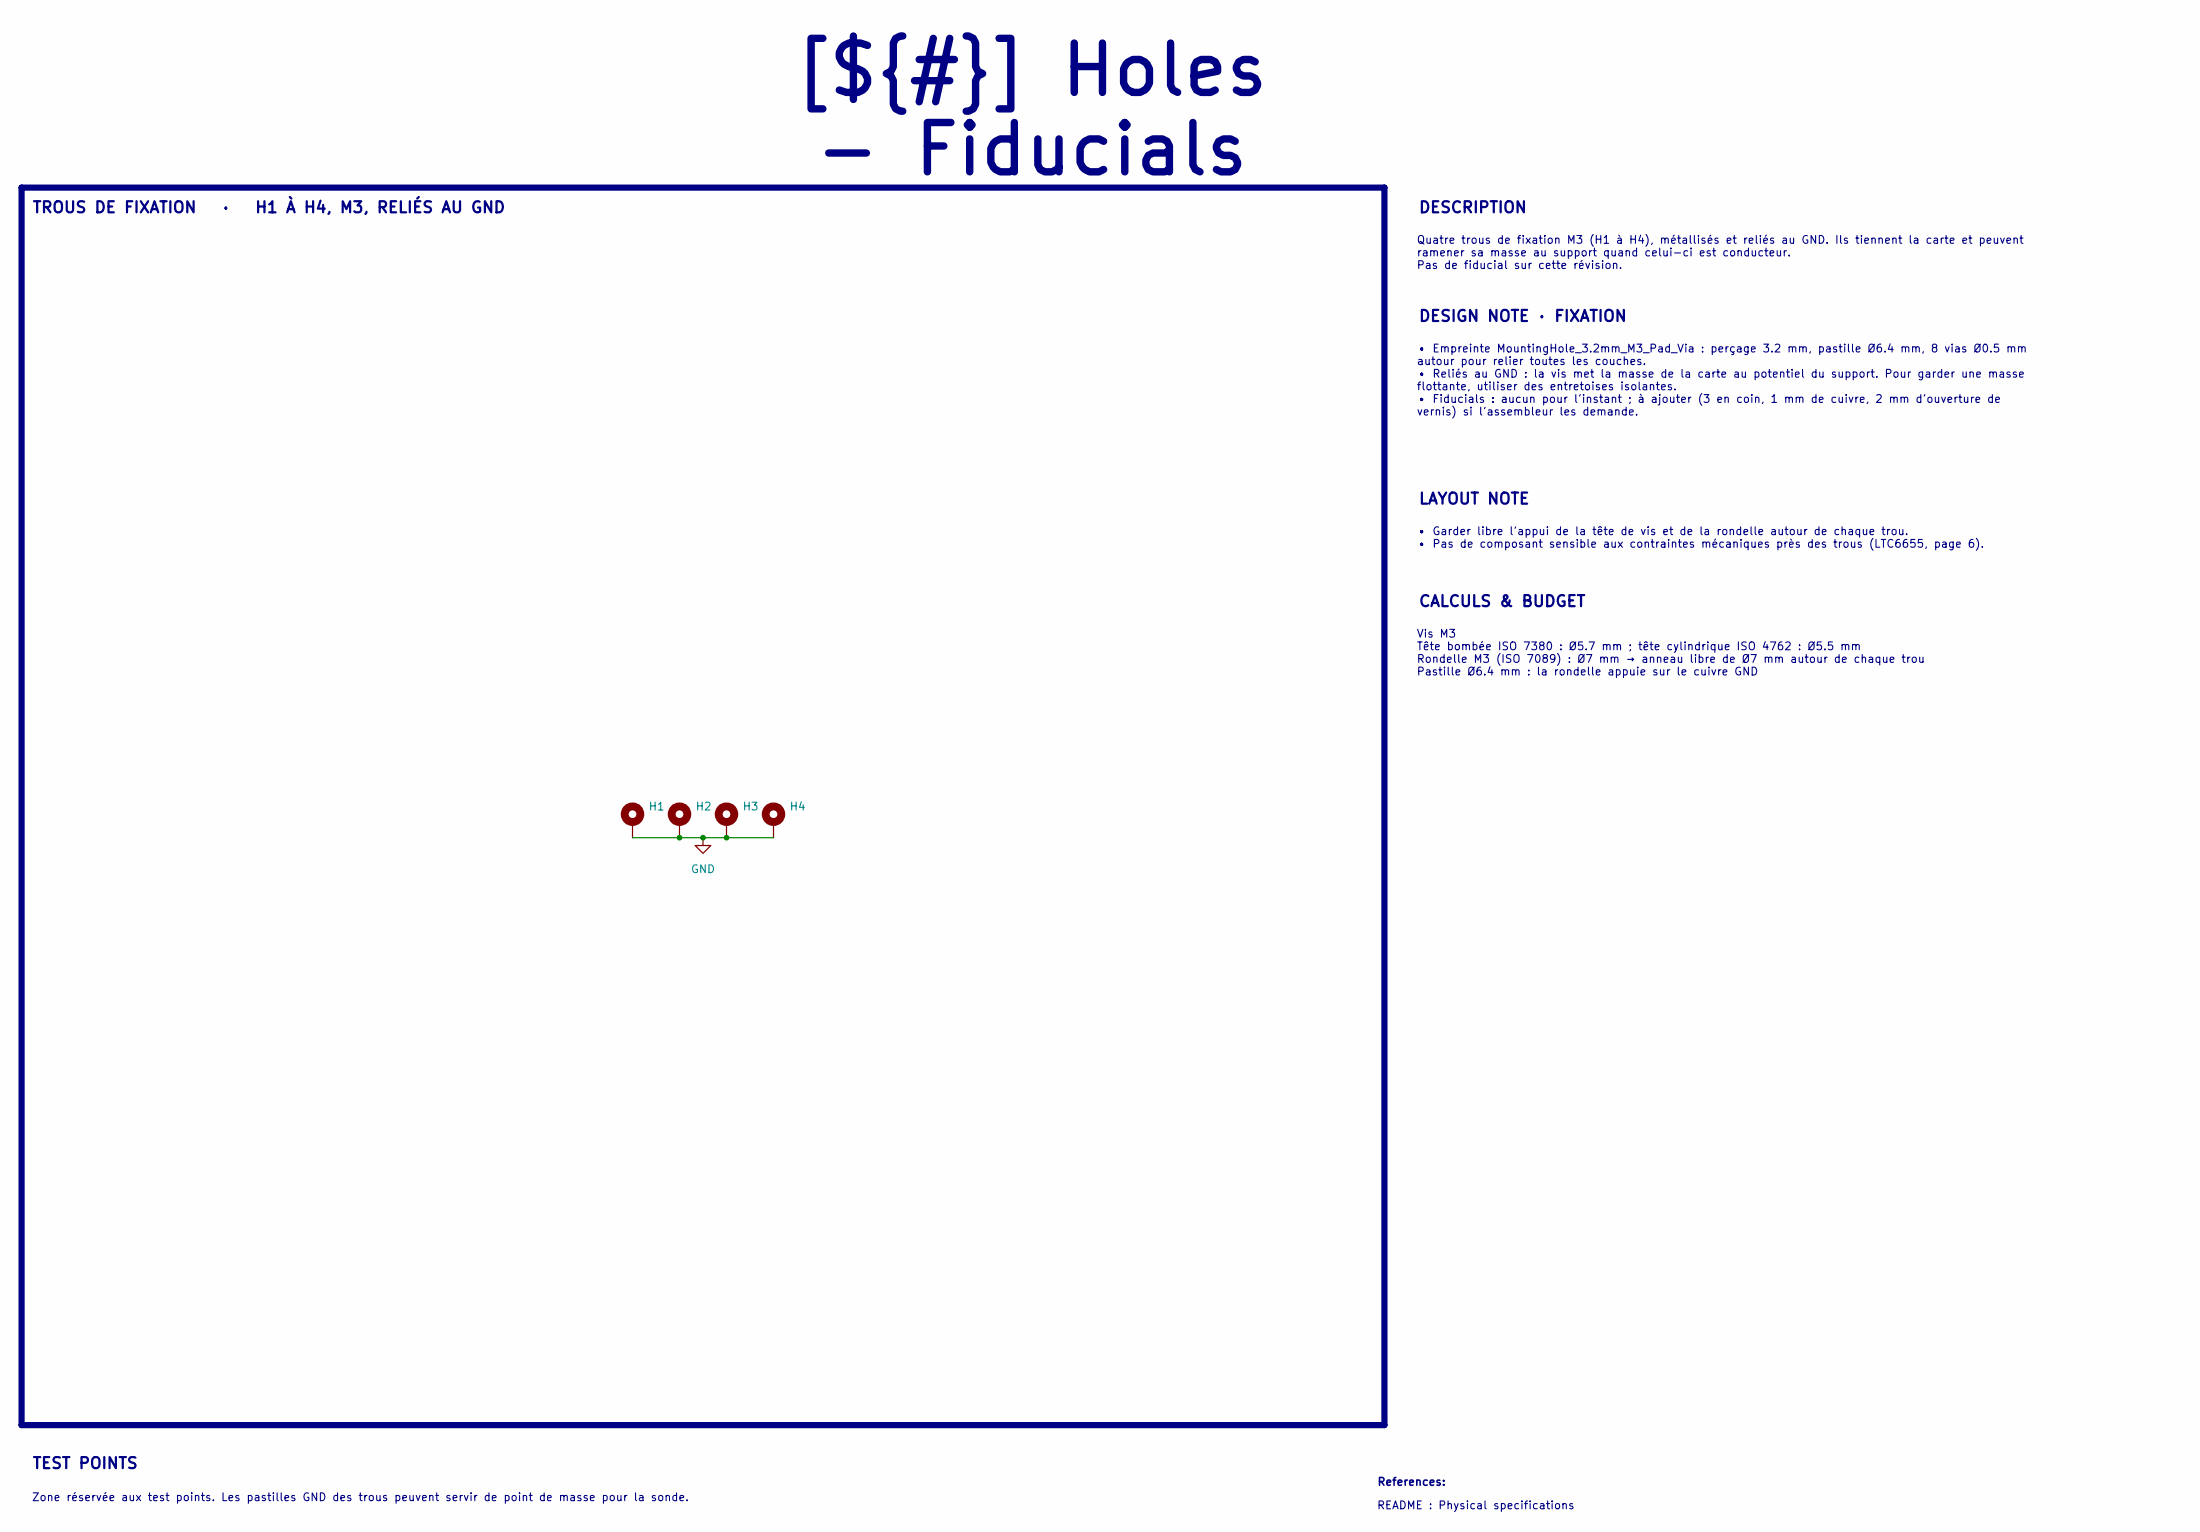
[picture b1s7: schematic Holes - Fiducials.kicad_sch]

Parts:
H1, H2, H3, H4: MountingHole_Pad; MountingHole_3.2mm_M3_Pad_Via

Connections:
GND: H1.1 (1_1), H2.1 (1_1), H3.1 (1_1), H4.1 (1_1); also elsewhere on the board

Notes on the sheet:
References:
README : Physical specifications
TEST POINTS
CALCULS & BUDGET
Quatre trous de fixation M3 (H1 à H4), métallisés et reliés au GND. Ils tiennent la carte et peuvent ramener sa masse au support quand celui-ci est conducteur. Pas de fiducial sur cette révision.
DESCRIPTION
TROUS DE FIXATION · H1 À H4, M3, RELIÉS AU GND
[${#}] ${TITLE}
LAYOUT NOTE
DESIGN NOTE · FIXATION
Vis M3 Tête bombée ISO 7380 : Ø5.7 mm ; tête cylindrique ISO 4762 : Ø5.5 mm Rondelle M3 (ISO 7089) : Ø7 mm → anneau libre de Ø7 mm autour de chaque trou Pastille Ø6.4 mm : la rondelle appuie sur le cuivre GND
• Empreinte MountingHole_3.2mm_M3_Pad_Via : perçage 3.2 mm, pastille Ø6.4 mm, 8 vias Ø0.5 mm autour pour relier toutes les couches. • Reliés au GND : la vis met la masse de la carte au potentiel du support. Pour garder une masse flottante, utiliser des entretoises isolantes. • Fiducials : aucun pou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
Zone réservée aux test points. Les pastilles GND des trous peuvent servir de point de masse pour la sonde.
• Garder libre l'appui de la tête de vis et de la rondelle autour de chaque trou. • Pas de composant sensible aux contraintes mécaniques près des trous (LTC6655, page 6).

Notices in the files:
README.md:
LICENSE:
The hardware design files in this repository are released under the **CERN Open Hardware Licence Version 2 – Permissive (CERN-OHL-P v2)**. See [LICENSE](LICENSE) for the full licence text.
Copyright 2026 Dimitry Siebert, OPEN THRUST LAB. Source location: .
Under CERN-OHL-P v2:
- You may use, study, modify and manufacture this design freely
- Derivative works do **not** need to remain open source
- Modified files must carry a notice stating that they were modified, with the date and a short description of the changes
- The original copyright and licen
License: CERN-OHL-P v2
